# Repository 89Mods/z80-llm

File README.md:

# What?

Z80-LLM is a bunch of code meant to enable a Z80 CPU to run a GPT-2-Medium sized LLM, but larger should theoretically be possible. This will hopefully finally bring modern AI into the retro-computing era. The code is written in simple C and should be easily portable to platforms not just based on the Z80, but also other retro CPUs with a C compiler toolchain.

# Why?

# How?

## Hardware

The demo hardware consist only of a Z80, 32KiB of ROM and some SRAM. 32KiB is not enough, so the final 16KiB of the address range is paged 16-ways to get a bit more. Though technically less memory usage is possible at the cost of speed. Obviously, running a LLM requires still more memory, so two PIO chips drive a PATA interface to a disk drive, where data is paged in and out of raw disk blocks to get even more space for matrices and vectors. Part of the disk is formated, though, to hold the network parameters.

Two UARTs are provided: one for standard output and a second to print a verbose log.

The schematics and PCB layout files can be found in the folder `Hardware`.

## LLM

The code to pre-train the LLM was written using libtorch in C++, using custom code for implementation of the attention layers, to make translating it into standalone C easier. This code was then supplied with a dataset of book texts and trained on a cloud compute instance containing a RTX4090 that was fed a large budget of 27.16$. The resulting LLM is good enough at generating basic, coherent text for the purposes of demonstration.

This code can be found in the folder `libtorch_llm`.

## Standalone C program

I started out by writing a standalone, single file C program on my desktop PC that can run the LLM, to have a working reference point when writing the code for the Z80.
Still, this program already contains key aspects of what is required on the Z80, such as parsing parameters from files and emulating matrices being stored in a block device.
The resulting code only depends on the standard library and compiles into a tiny executable on Linux.

This code can be found in the folder `c_pgm`.

## Z80 Firmware

z88dk was used to create the program to run the LLM on a Z80. It works as described above by using space on a connected disk drive as memory for matrices and the paged SRAM as cache for that memory. To load the parameters, a filesystem partition is also present on the disk. My choice of filesystem is, of course, ext4, to further modernize the software design. Only basic filesystem read access is supported, but code to handle checksum checking and symlink parsing is present and can be enabled, if required. This allows easy copying and modification of the network parameters on the disk from any common Linux distro!

Standard IEEE 32-bit floats are used for computation. I did experiment with 16-bit floats and fixed-point numbers, but they produced completely broken results due to precission errors. So floats are used, for maximum compatibility! Though, one optimization I did make use of is LUTs. Notably, the GeLU nonlinearity is implemented through a LUT in a file, which I found to be faster.

A byte-pair-encoder almost identical to the one used in GPT-2 is used for tokenization. I will admit, the code I wrote for it is not the best, but it successfully runs on the Z80, so I am happy with it. It also uses data stored on the filesystem to do the encoding.

Note: the resulting code does not fit into the 32KiB ROM. To work around this, the CPU copies some blocks from the disk to SRAM at bootup, allowing code to overflow into RAM. Any code changes require not only re-programming of the ROM, but also an update of the disk image. I apologize for this inconvenience.

This code can be found in the folder `Z80`.

# Speed

At 8MHz and using a SSD as the disk drive for maximum throughput, I have approximated, using simulation, a time of 1,292,518 minutes per token, or roughly 2.4 years. Upgrading to a 20MHz Z80 should cut that down to 1 year, and I am investigating speeds using a AM9511 to accelerate the floating-point computations.

# Usage

The intended method for getting this beast running is to put together a disk image on your PC, and then dd-ing it to a real drive. Open a terminal at the root of this repository.

First, create a blank file that is less than or equal in capacity to your target physical drive. I am using a SSD with slightly less than 16GiB capacity, so I will use a 3G large image: `dd if=/dev/zero of=./disk.img bs=1M count=3072`

Next, it needs a filesystem partition. It can’t span the whole disk, as the program requires a bit of free space after the filesystem partition, which it will use as memory. Use fdisk for this: `fdisk ./disk.img`

Create a MBR partition table (`o`) and add a new partition (`n`), which is to be primary (`p`) and number 1 (`1`). First sector has to be 2048, as the first blocks of the disk past the MBR will store Z80 bytecode that is overflowing from ROM into RAM. For the size of the partition, I go with 2G (`+2G`) so mkfs doesn’t make a fuzz on the next step.

`w` will tell fdisk to write changes to the disk image and exit. To continue, the disk image needs to be set up as a loop device, so it can be worked on directly: `sudo losetup -fP disk.img`. For the next steps, make sure you are targeting the correct device, or you may corrupt a part of your OS! `lsblk` shows one new device, `loop0`, after the previous command, so that has to be it.

Simply doing `sudo mkfs.ext4 /dev/loop0p1` will create the ext4 file system on the partition that was just created. Note: it is possible your distro’s mkfs config enables filesystem features not supported by my code. If this happens, you can comment out the FS feature check in `Z80/ext4.c`. In most cases, it will still work.

At this point, you should be able to minimize the terminal window and continue in your DE’s file browser, as the freshly formatted partition should show up there, like a removable drive. Open it. You can change the permissions to make these next steps easier if you want, it won’t affect things on the Z80.

For now, I will only describe how to install the weights from my pre-trained model. Download the files [here](https://files.tholin.dev/Public/model.tar.gz) and extract into the root of the partition.

Next is the data files for the tokenizer. Navigate to `libtorch_llm/data/` directory and simply run the `prepare_vocab.sh` bash script. I decided to use GPT-2’s actual tokenizer configs, and this script will download them and apply any required modifications. You can then copy the entire `data` folder to the root of the ext4 partition.

Note: you will need nodejs installed to run one of the helper scripts. Yes, I am aware of how absolutely insane the language spread of this repository is.

Once done, the root of the partition should have three entries `LUTs`, `model` and `data`. You can now un-mount the partition. To remove the loop device, I like to use this handy command, which destroys all loop devices associated with a specific file: `losetup -j ./disk.img | grep -o "/dev/loop[0-9][0-9]*" | xargs -L1 sudo losetup -d`.

Now, finally, comes the step of building the Z80 code. Start by installing [z88dk](https://github.com/z88dk/z88dk/) in whichever way you prefer. Then, navigate a terminal to the `Z80` directory in this repo and simply do `make`. The makefile should do everything for you, including modifying the disk image with the overflowing binary (assuming you created it in the right place).

Lastly, get out whatever ROM programmer you use and burn `EPROM.bin` onto a memory chip of your choice. In parallel, start copying the disk image to a real drive, preferably through dd.

Congratulations! You are now ready to wait 2.5 years for your Z80 to say a single word to you!

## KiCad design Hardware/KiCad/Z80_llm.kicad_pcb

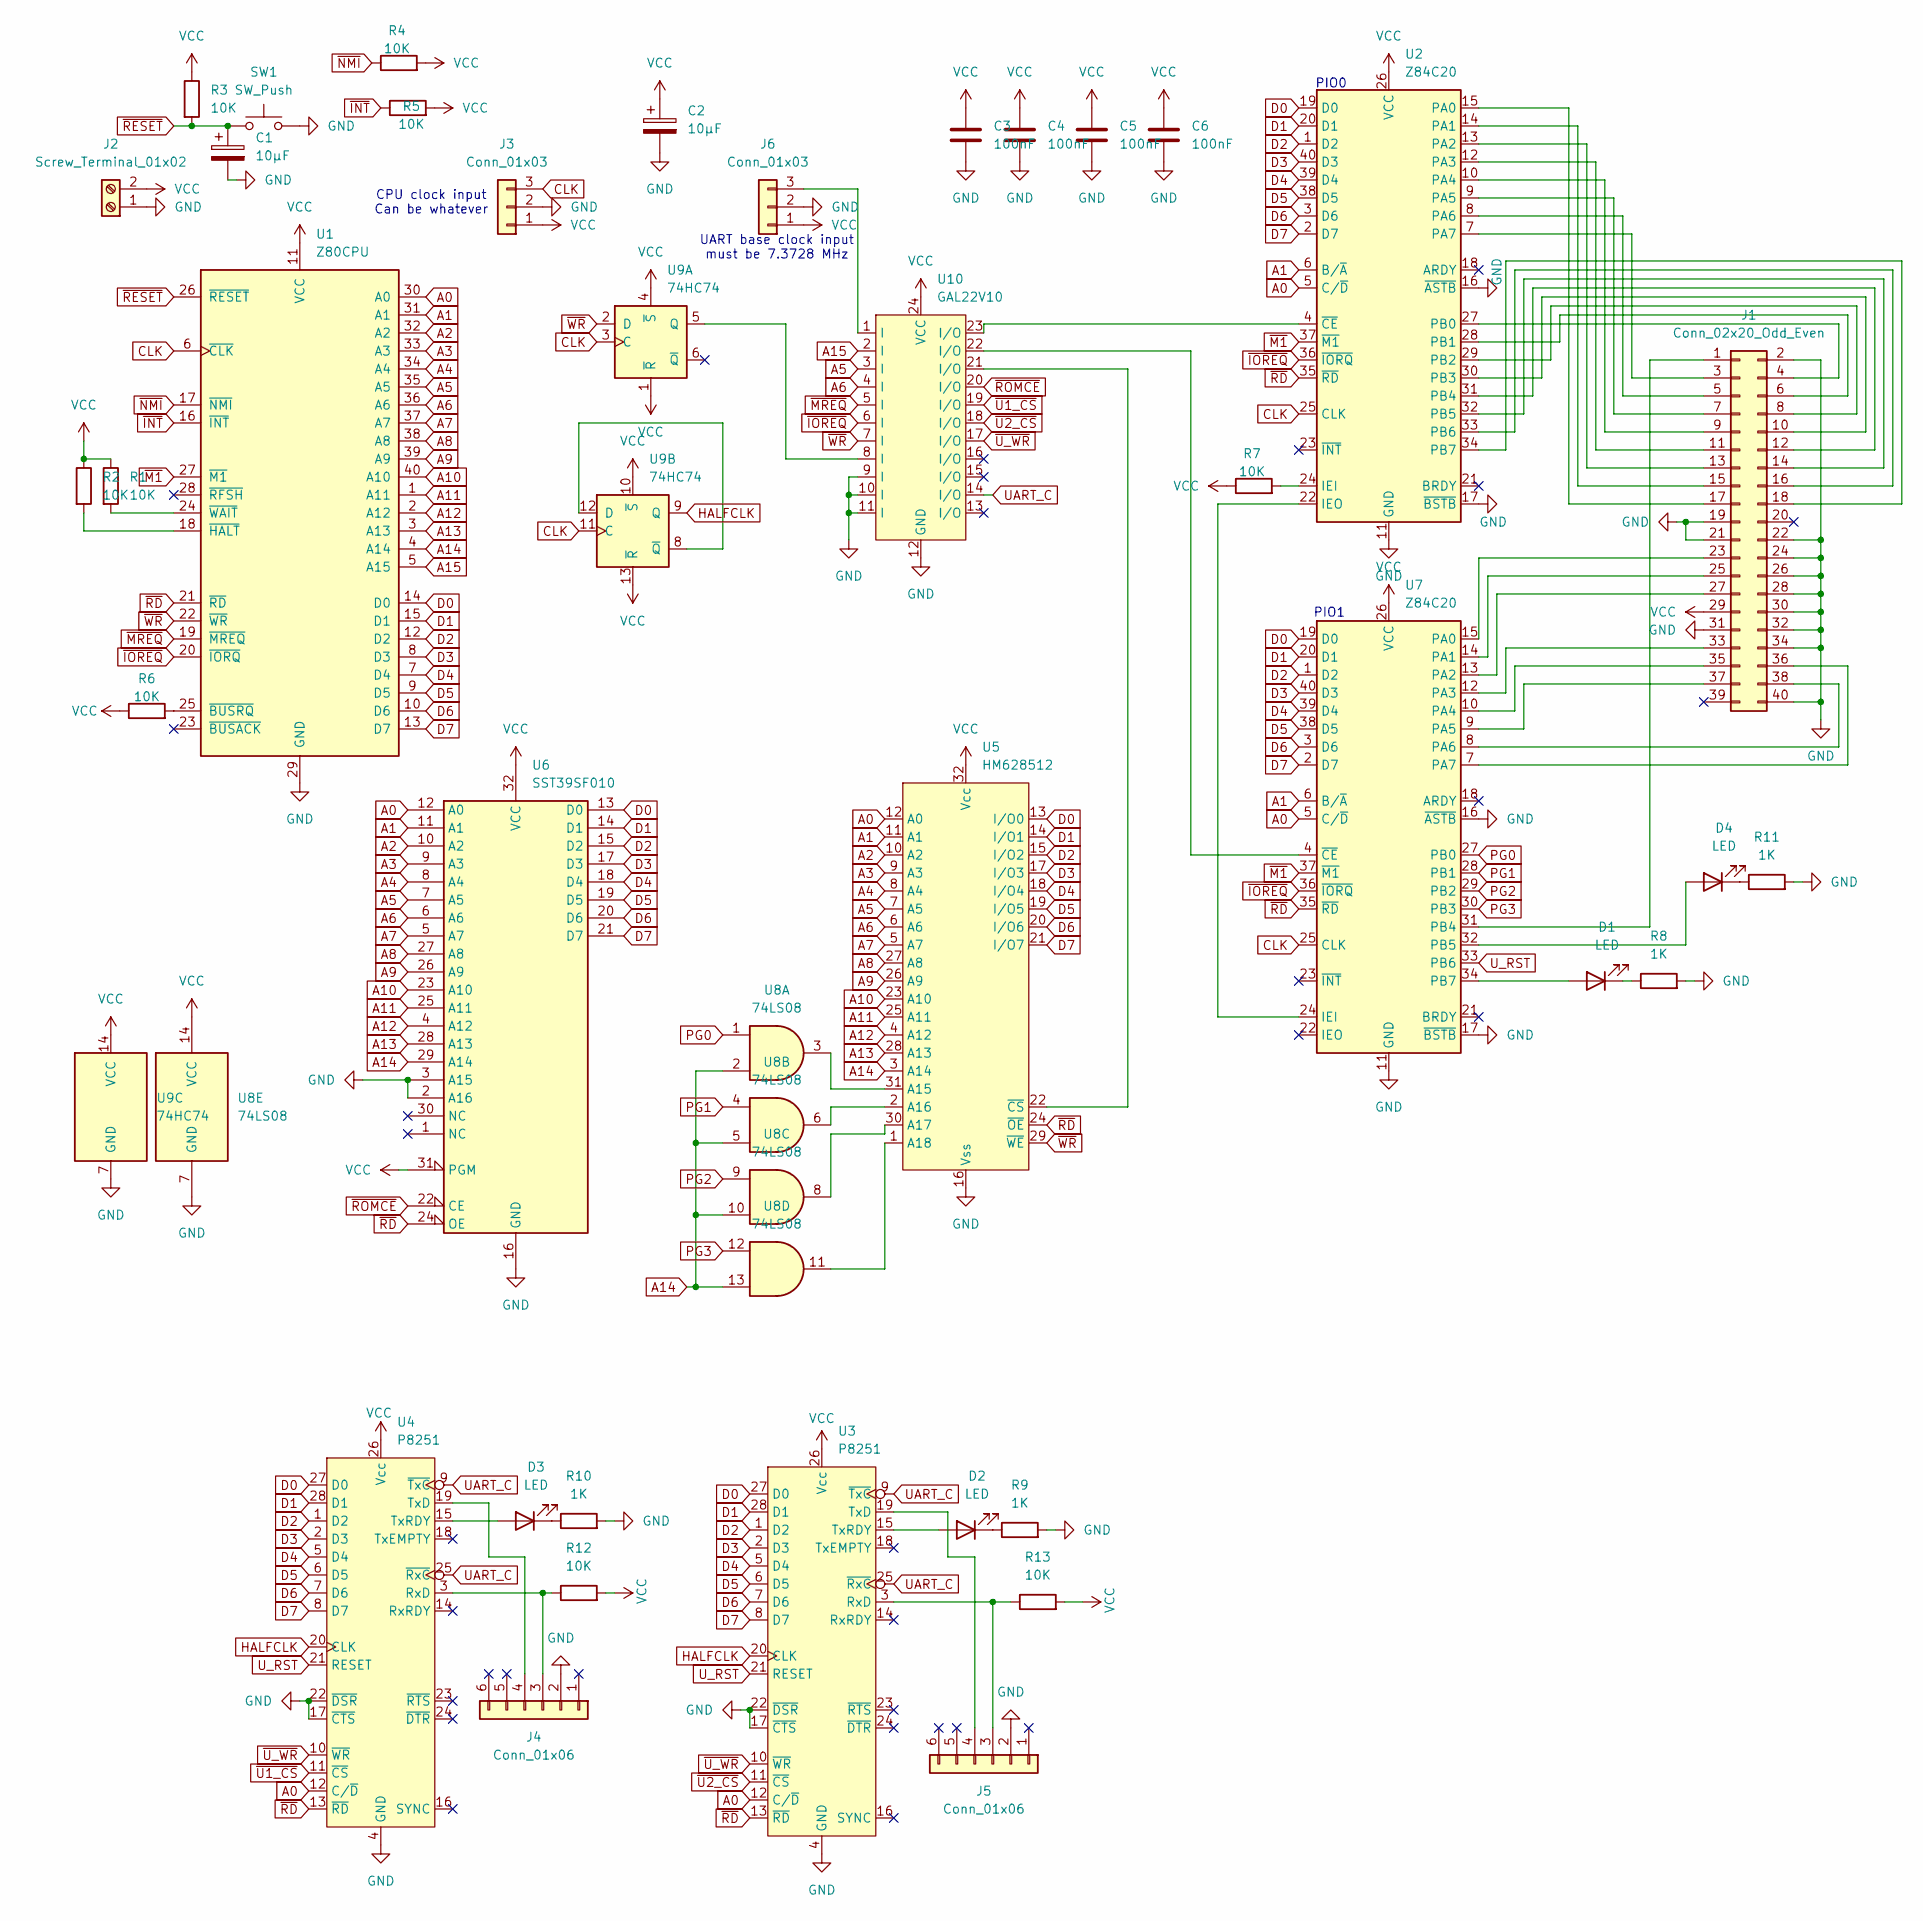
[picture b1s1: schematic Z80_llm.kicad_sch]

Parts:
C1, C2: 10µF; CP_Radial_D4.0mm_P2.00mm
C3, C4, C5, C6: 100nF; C_0805_2012Metric_Pad1.18x1.45mm_HandSolder
D1: LED; LED_D5.0mm
D2, D3, D4: LED; LED_D3.0mm
J1: Conn_02x20_Odd_Even; PinHeader_2x20_P2.54mm_Vertical
J2: Screw_Terminal_01x02; TerminalBlock_bornier-2_P5.08mm
J3, J6: Conn_01x03; PinHeader_1x03_P2.54mm_Vertical
J4, J5: Conn_01x06; PinHeader_1x06_P2.54mm_Vertical
R1, R2, R3, R4, R5, R6, R7, R12, R13: 10K; R_1206_3216Metric_Pad1.30x1.75mm_HandSolder
R8, R9, R10, R11: 1K; R_1206_3216Metric_Pad1.30x1.75mm_HandSolder
SW1: SW_Push; SW_PUSH_6mm
U1: Z80CPU; DIP-40_W15.24mm
U2, U7: Z84C20; DIP-40_W15.24mm
U3, U4: P8251; DIP-28_W15.24mm
U5: HM628512; DIP-32_W15.24mm
U6: SST39SF010; DIP-32_W15.24mm
U8: 74LS08; SO-14_3.9x8.65mm_P1.27mm
U9: 74HC74; DIP-14_W7.62mm
U10: GAL22V10; DIP-24_W7.62mm_Socket

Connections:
A0: U1.30 (A0), U2.5 (C/~D), U3.12 (C/~D), U4.12 (C/~D), U5.12 (A0), U6.12 (A0), U7.5 (C/~D)
A1: U1.31 (A1), U2.6 (B/~A), U5.11 (A1), U6.11 (A1), U7.6 (B/~A)
A2: U1.32 (A2), U5.10 (A2), U6.10 (A2)
A3: U1.33 (A3), U5.9 (A3), U6.9 (A3)
A4: U1.34 (A4), U5.8 (A4), U6.8 (A4)
A5: U1.35 (A5), U5.7 (A5), U6.7 (A5), U10.3 (I)
A6: U1.36 (A6), U5.6 (A6), U6.6 (A6), U10.4 (I)
A7: U1.37 (A7), U5.5 (A7), U6.5 (A7)
A8: U1.38 (A8), U5.27 (A8), U6.27 (A8)
A9: U1.39 (A9), U5.26 (A9), U6.26 (A9)
A10: U1.40 (A10), U5.23 (A10), U6.23 (A10)
A11: U1.1 (A11), U5.25 (A11), U6.25 (A11)
A12: U1.2 (A12), U5.4 (A12), U6.4 (A12)
A13: U1.3 (A13), U5.28 (A13), U6.28 (A13)
A14: U1.4 (A14), U5.3 (A14), U6.29 (A14), U8.2, U8.5, U8.10, U8.13
A15: U1.5 (A15), U10.2 (I)
CLK: J3.3, U1.6 (~CLK), U2.25 (CLK), U7.25 (CLK), U9.3 (C), U9.11 (C)
D0: U1.14 (D0), U2.19 (D0), U3.27 (D0), U4.27 (D0), U5.13 (I/O0), U6.13 (D0), U7.19 (D0)
D1: U1.15 (D1), U2.20 (D1), U3.28 (D1), U4.28 (D1), U5.14 (I/O1), U6.14 (D1), U7.20 (D1)
D2: U1.12 (D2), U2.1 (D2), U3.1 (D2), U4.1 (D2), U5.15 (I/O2), U6.15 (D2), U7.1 (D2)
D3: U1.8 (D3), U2.40 (D3), U3.2 (D3), U4.2 (D3), U5.17 (I/O3), U6.17 (D3), U7.40 (D3)
D4: U1.7 (D4), U2.39 (D4), U3.5 (D4), U4.5 (D4), U5.18 (I/O4), U6.18 (D4), U7.39 (D4)
D5: U1.9 (D5), U2.38 (D5), U3.6 (D5), U4.6 (D5), U5.19 (I/O5), U6.19 (D5), U7.38 (D5)
D6: U1.10 (D6), U2.3 (D6), U3.7 (D6), U4.7 (D6), U5.20 (I/O6), U6.20 (D6), U7.3 (D6)
D7: U1.13 (D7), U2.2 (D7), U3.8 (D7), U4.8 (D7), U5.21 (I/O7), U6.21 (D7), U7.2 (D7)
GND: C1.2, C2.2, C3.2, C4.2, C5.2, C6.2, J1.2, J1.19, J1.21, J1.22, J1.24, J1.26, J1.28, J1.30, J1.31, J1.32, J1.34, J1.40, J2.1, J3.2, J4.2, J5.2, J6.2, R8.2, R9.2, R10.2, R11.2, SW1.2, U1.29 (GND), U2.11 (GND), U2.16 (~ASTB), U2.17 (~BSTB), U3.4 (GND), U3.17 (~CTS), U3.22 (~DSR), U4.4 (GND), U4.17 (~CTS), U4.22 (~DSR), U5.16 (Vss), U6.2 (A16), U6.3 (A15), U6.16 (GND), U7.11 (GND), U7.16 (~ASTB), U7.17 (~BSTB), U8.7 (GND), U9.7 (GND), U10.9 (I), U10.10 (I), U10.11 (I), U10.12 (GND)
HALFCLK: U3.20 (CLK), U4.20 (CLK), U9.9 (Q)
unnamed: D1.2 (A), U7.34 (PB7)
unnamed: D1.1 (K), R8.1
unnamed: D2.2 (A), U3.15 (TxRDY)
unnamed: D2.1 (K), R9.1
unnamed: D3.2 (A), U4.15 (TxRDY)
unnamed: D3.1 (K), R10.1
unnamed: D4.2 (A), U7.32 (PB5)
unnamed: D4.1 (K), R11.1
unnamed: J1.1, U7.31 (PB4)
unnamed: J1.3, U2.7 (PA7)
unnamed: J1.4, U2.27 (PB0)
unnamed: J1.5, U2.8 (PA6)
unnamed: J1.6, U2.28 (PB1)
unnamed: J1.7, U2.9 (PA5)
unnamed: J1.8, U2.29 (PB2)
unnamed: J1.9, U2.10 (PA4)
unnamed: J1.10, U2.30 (PB3)
unnamed: J1.11, U2.12 (PA3)
unnamed: J1.12, U2.31 (PB4)
unnamed: J1.13, U2.13 (PA2)
unnamed: J1.14, U2.32 (PB5)
unnamed: J1.15, U2.14 (PA1)
unnamed: J1.16, U2.33 (PB6)
unnamed: J1.17, U2.15 (PA0)
unnamed: J1.18, U2.34 (PB7)
unnamed: J1.23, U7.15 (PA0)
unnamed: J1.25, U7.14 (PA1)
unnamed: J1.27, U7.13 (PA2)
unnamed: J1.33, U7.12 (PA3)
unnamed: J1.35, U7.10 (PA4)
unnamed: J1.36, U7.7 (PA7)
unnamed: J1.37, U7.9 (PA5)
unnamed: J1.38, U7.8 (PA6)
unnamed: J4.3, R12.1, U4.3 (RxD)
unnamed: J4.4, U4.19 (TxD)
unnamed: J5.3, R13.1, U3.3 (RxD)
unnamed: J5.4, U3.19 (TxD)
unnamed: J6.3, U10.1 (I)
unnamed: R6.2, U1.25 (~BUSRQ)
unnamed: R2.2, U1.18 (~HALT)
unnamed: R1.2, U1.24 (~WAIT)
unnamed: R7.2, U2.24 (IEI)
unnamed: U2.22 (IEO), U7.24 (IEI)
unnamed: U2.4 (~CE), U10.23 (I/O)
unnamed: U5.31 (A15), U8.3
unnamed: U5.2 (A16), U8.6
unnamed: U5.30 (A17), U8.8
unnamed: U5.1 (A18), U8.11
unnamed: U5.22 (~CS), U10.21 (I/O)
unnamed: U7.4 (~CE), U10.22 (I/O)
unnamed: U9.5 (Q), U10.8 (I)
unnamed: U9.8 (~Q), U9.12 (D)
PG0: U7.27 (PB0), U8.1
PG1: U7.28 (PB1), U8.4
PG2: U7.29 (PB2), U8.9
PG3: U7.30 (PB3), U8.12
UART_C: U3.9 (~TxC), U3.25 (~RxC), U4.9 (~TxC), U4.25 (~RxC), U10.14 (I/O)
U_RST: U3.21 (RESET), U4.21 (RESET), U7.33 (PB6)
VCC: C2.1, C3.1, C4.1, C5.1, C6.1, J1.29, J2.2, J3.1, J6.1, R1.1, R2.1, R3.1, R4.2, R5.2, R6.1, R7.1, R12.2, R13.2, U1.11 (VCC), U2.26 (VCC), U3.26 (Vcc), U4.26 (Vcc), U5.32 (Vcc), U6.31 (PGM), U6.32 (VCC), U7.26 (VCC), U8.14 (VCC), U9.1 (~R), U9.4 (~S), U9.10 (~S), U9.13 (~R), U9.14 (VCC), U10.24 (VCC)
~INT: R5.1, U1.16 (~INT)
~IOREQ: U1.20 (~IORQ), U2.36 (~IORQ), U7.36 (~IORQ), U10.6 (I)
~M1: U1.27 (~M1), U2.37 (~M1), U7.37 (~M1)
~MREQ: U1.19 (~MREQ), U10.5 (I)
~NMI: R4.1, U1.17 (~NMI)
~RD: U1.21 (~RD), U2.35 (~RD), U3.13 (~RD), U4.13 (~RD), U5.24 (~OE), U6.24 (OE), U7.35 (~RD)
~RESET: C1.1, R3.2, SW1.1, U1.26 (~RESET)
~ROMCE: U6.22 (CE), U10.20 (I/O)
~U1_CS: U4.11 (~CS), U10.19 (I/O)
~U2_CS: U3.11 (~CS), U10.18 (I/O)
~U_WR: U3.10 (~WR), U4.10 (~WR), U10.17 (I/O)
~WR: U1.22 (~WR), U5.29 (~WE), U9.2 (D), U10.7 (I)

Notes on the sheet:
UART base clock input must be 7.3728 MHz
CPU clock input Can be whatever
PIO0
PIO1

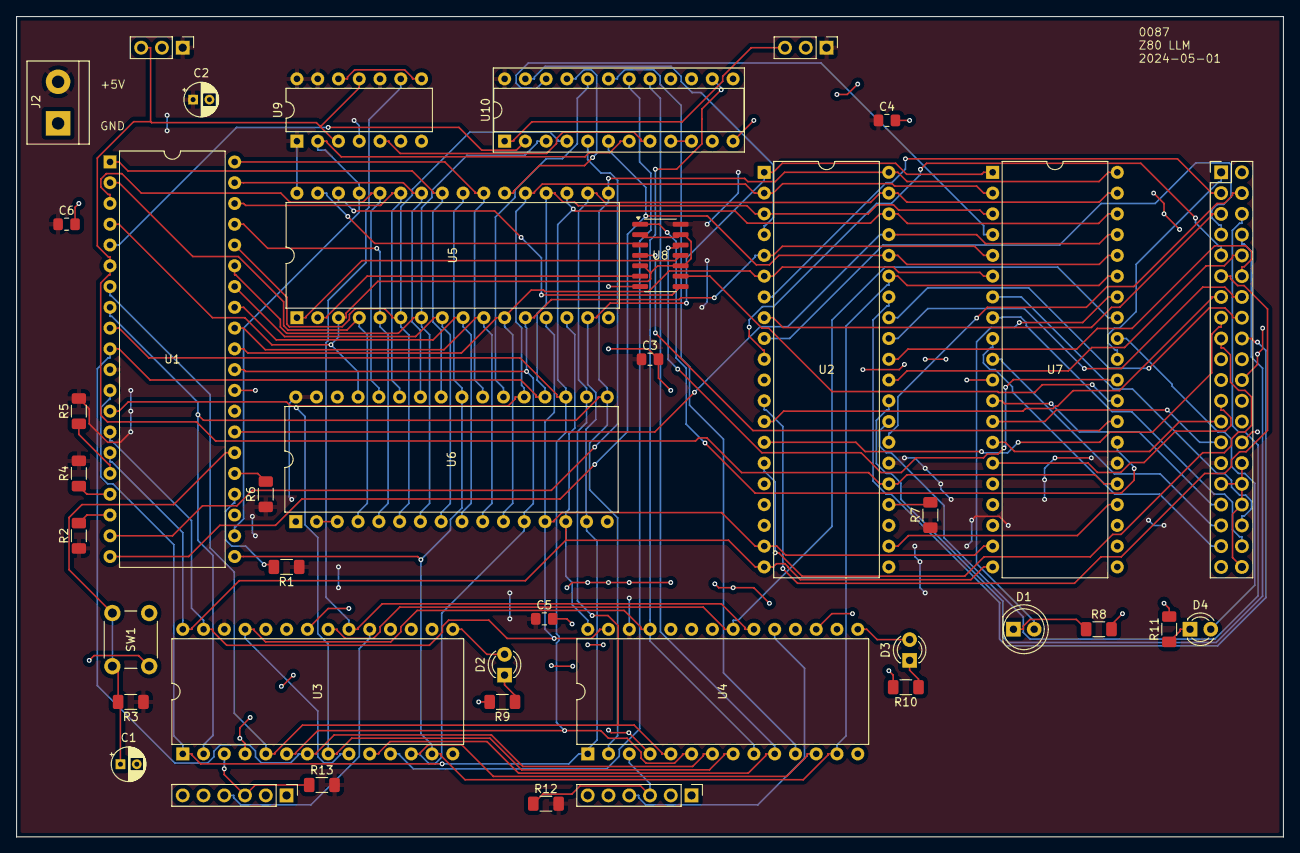
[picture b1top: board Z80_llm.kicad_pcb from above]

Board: 2 copper layers, 154.9 x 100.3 mm, 40 parts (0 on the bottom side), 98 nets.

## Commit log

2024-10-27 Initial
2024-10-27 Setup guide
